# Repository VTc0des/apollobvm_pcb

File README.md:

# Notes:
* Pause button on master has to go to digital pin 10 to allow for bootload.
* 47 uF caps on voltage regulator
* Diode on output from voltage regulator for programming
* Ground for programming port with labels
* Change to DPAK package for voltage regulator for better thermal properties
* Heat sync voltage regulator on ground plane

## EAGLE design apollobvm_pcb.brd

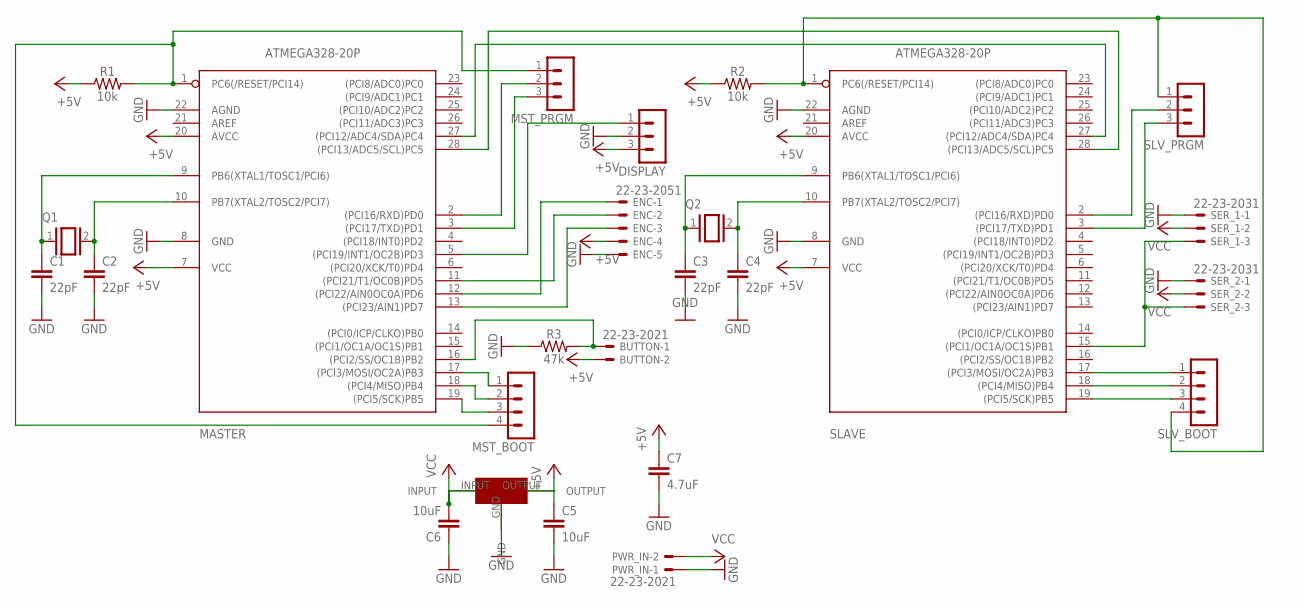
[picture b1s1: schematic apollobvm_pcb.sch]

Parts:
BUTTON: 22-23-2021
C1, C2, C3, C4: 22pF; 0603
C5, C6: 10uF; 0603
C7: 4.7uF; 0603
DISPLAY: MA03-1
ENC: 22-23-2051
MASTER: ATMEGA328-20P; DIL28-3
MST_BOOT: MA04-1
MST_PRGM: MA03-1
PWR_IN: 22-23-2021
Q1, Q2: XTAL/S; QS
R1, R2: 10k; 0603
R3: 47k; 0603
SER_1, SER_2: 22-23-2031
SLAVE: ATMEGA328-20P; DIL28-3
SLV_BOOT: MA04-1
SLV_PRGM: MA03-1
U$1: NCP1117

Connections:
+5V: BUTTON.2, C5.1, C7.1, DISPLAY.3, ENC.4, MASTER.7 (VCC), MASTER.20 (AVCC), R1.1, R2.1, SLAVE.7 (VCC), SLAVE.20 (AVCC), U$1.OUTPUT
GND: C1.2, C2.2, C3.2, C4.2, C5.2, C6.1, C7.2, DISPLAY.2, ENC.5, MASTER.8 (GND), MASTER.22 (AGND), PWR_IN.1, R3.1, SER_1.1, SER_2.1, SLAVE.8 (GND), SLAVE.22 (AGND), U$1.GND
unnamed: MASTER.1 (PC6(/RESET/PCI14)), MST_BOOT.4, MST_PRGM.1, R1.2
unnamed: R2.2, SLAVE.1 (PC6(/RESET/PCI14)), SLV_BOOT.4, SLV_PRGM.1
unnamed: C3.1, Q2.1, SLAVE.9 (PB6(XTAL1/TOSC1/PCI6))
unnamed: C4.1, Q2.2, SLAVE.10 (PB7(XTAL2/TOSC2/PCI7))
unnamed: C1.1, MASTER.9 (PB6(XTAL1/TOSC1/PCI6)), Q1.1
unnamed: C2.1, MASTER.10 (PB7(XTAL2/TOSC2/PCI7)), Q1.2
unnamed: SER_1.3, SER_2.3, SLAVE.15 ((PCI1/OC1A/OC1S)PB1)
unnamed: DISPLAY.1, MASTER.5 ((PCI19/INT1/OC2B)PD3)
unnamed: ENC.3, MASTER.13 ((PCI23/AIN1)PD7)
unnamed: ENC.2, MASTER.11 ((PCI21/T1/OC0B)PD5)
unnamed: MASTER.27 ((PCI12/ADC4/SDA)PC4), SLAVE.27 ((PCI12/ADC4/SDA)PC4)
unnamed: ENC.1, MASTER.12 ((PCI22/AIN0OC0A)PD6)
unnamed: MASTER.28 ((PCI13/ADC5/SCL)PC5), SLAVE.28 ((PCI13/ADC5/SCL)PC5)
unnamed: BUTTON.1, MASTER.16 ((PCI2/SS/OC1B)PB2), R3.2
unnamed: SLAVE.17 ((PCI3/MOSI/OC2A)PB3), SLV_BOOT.1
unnamed: SLAVE.18 ((PCI4/MISO)PB4), SLV_BOOT.2
unnamed: SLAVE.19 ((PCI5/SCK)PB5), SLV_BOOT.3
unnamed: MASTER.17 ((PCI3/MOSI/OC2A)PB3), MST_BOOT.1
unnamed: MASTER.18 ((PCI4/MISO)PB4), MST_BOOT.2
unnamed: MASTER.19 ((PCI5/SCK)PB5), MST_BOOT.3
unnamed: SLAVE.2 ((PCI16/RXD)PD0), SLV_PRGM.2
unnamed: SLAVE.3 ((PCI17/TXD)PD1), SLV_PRGM.3
unnamed: MASTER.2 ((PCI16/RXD)PD0), MST_PRGM.2
unnamed: MASTER.3 ((PCI17/TXD)PD1), MST_PRGM.3
VCC: C6.2, PWR_IN.2, SER_1.2, SER_2.2, U$1.INPUT

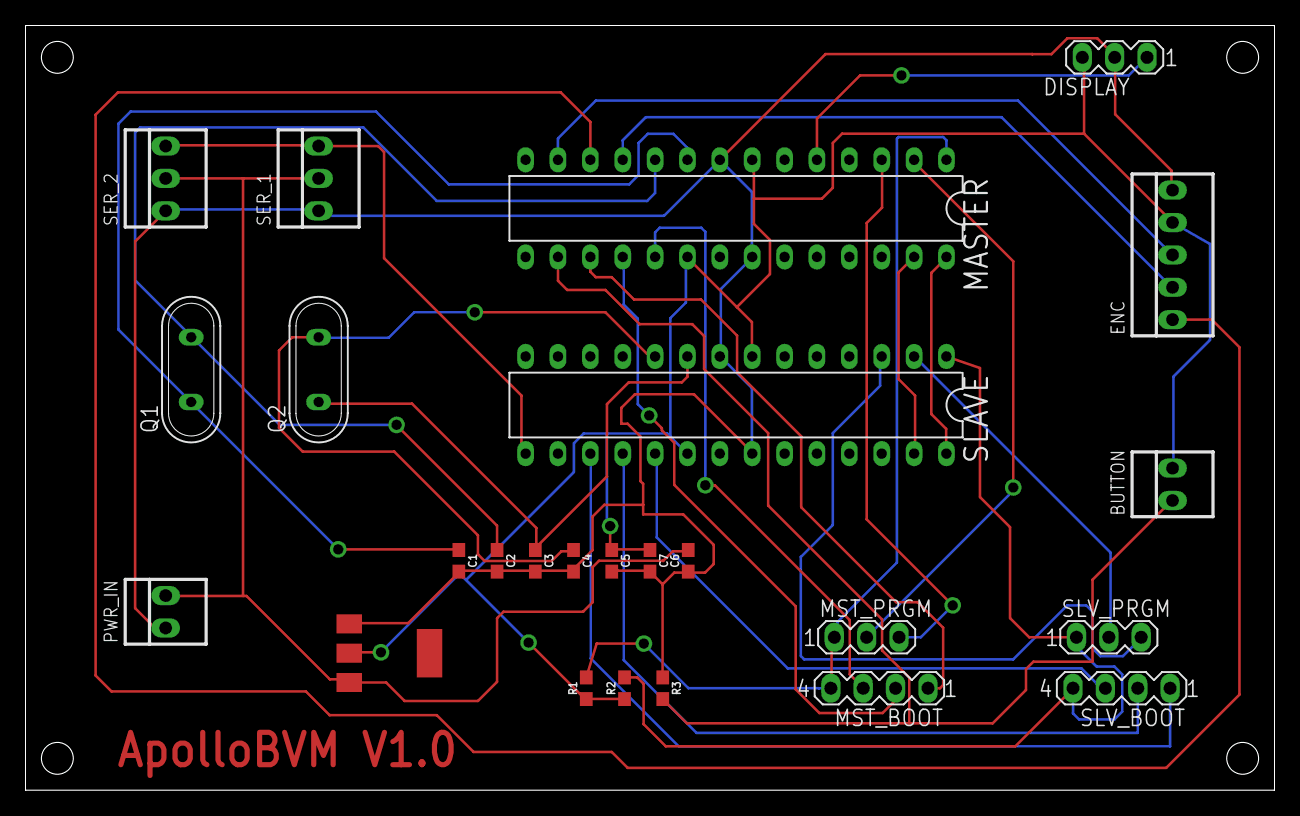
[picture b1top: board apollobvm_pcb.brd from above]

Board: 2 copper layers, 98.0 x 60.0 mm, 25 parts (0 on the bottom side), 27 nets.

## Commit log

2020-04-08 Added initial schematic
2020-04-08 Added board file
2020-04-08 Finished initial board
2020-04-08 Fixed some final issues with initial board
2020-04-08 Moved PWM leads apart for servos
2020-04-08 Added millable version
2020-04-10 Made board for milling
2020-04-10 Fixed close traces
2020-04-10 Updated bottom
2020-04-12 Increased trace size
2020-04-13 Syncing
2020-04-16 Added gerber files

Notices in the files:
parts and their libraries:
SparkFun-Capacitors: Licensing: Creative Commons ShareAlike 4.0 International - https://creativecommons.org/licenses/by-sa/4.0
